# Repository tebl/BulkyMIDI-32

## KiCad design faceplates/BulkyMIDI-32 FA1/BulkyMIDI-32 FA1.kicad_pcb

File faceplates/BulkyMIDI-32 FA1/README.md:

# BulkyMIDI-32 Faceplate (FA1)
A faceplate designed to be installed onto the main [BulkyMIDI-32](https://github.com/tebl/BulkyMIDI-32/tree/main/BulkyMIDI-32%20Module)-module. The faceplate has provisions for mounting two of the buttons onto the faceplate, the signals passing through the pin headers in the top-left corner. I consider this more of a usability option as you're never in doubt what is up and down, but at the cost of having a cleaner finish on the faceplate itself. If all of this sounds rather horrible, then check out [Faceplate FA2](https://github.com/tebl/BulkyMIDI-32/tree/main/faceplates/BulkyMIDI-32%20FA2) as you might prefer that as an alternative.

- [1> Building the device](#1-building-the-device)
- [2> Schematic](#2-schematic)
- [3> BOM](#3-bom)

# 1> Building the device
Building the device should be a straight forward affair, you just solder the two components into place. Pay attention to keep the alignment somewhat straight, in particular the right-angle pin header needs to be flush against the board. A picture of the board is shown below, pay particular attention to which side the components are installed.

When installing the switches here, you'd jumper SW4 on the main BulkyMIDI-32 to positions 2-3 when doing so. The default would otherwise be linked across pins 1-2 when four buttons are installed on the main module instead.

The faceplate connects to the main module using extra long male pin headers, but we need to pay attention so that the height of these are adjusted before soldering them in place. The easiest way of doing this is just to insert them into the socket and press down on the faceplate until the black plastic part slides down into place. Once satisfied with the result, solder them in place and cut off the excess part of the pins that are poking out of the top.

# 2> Schematic
The supplied KiCad files should be sufficient as both a schematic and as a  starting point for ordering PCBs (basically you could just zip the contents of the export folder and upload that on a fabrication site), the schematic is also available in [PDF-format](https://github.com/tebl/BulkyMIDI-32/tree/main/documentation/schematic/faceplates) and this is what you'll need to print and work your way through when things fail to work as expected.

# 3> BOM
Most parts should be easy to get a hold of from your favourite local electronic component shop, but given that I don't have access to such shops where I live so everything was based on whatever I could get cheapest from eBay/AliExpress (free shipping, but plan on waiting 3-4 weeks for delivery). 

| Reference      | Item                                                  | Count | Order  |
| ---------------| ----------------------------------------------------- | ----- | ------ |
| Faceplate PCB  | Fabricate using Gerber files                          |     1 | [PCBWay](https://www.pcbway.com/project/shareproject/BulkyMIDI_32_Faceplate_FA1_22c4404e.html)
| J1             | 1x10 section of long male header pins                 |     1 |
| SW1,SW2        | 6x6x11mm right-angle momentary button                 |     1 |

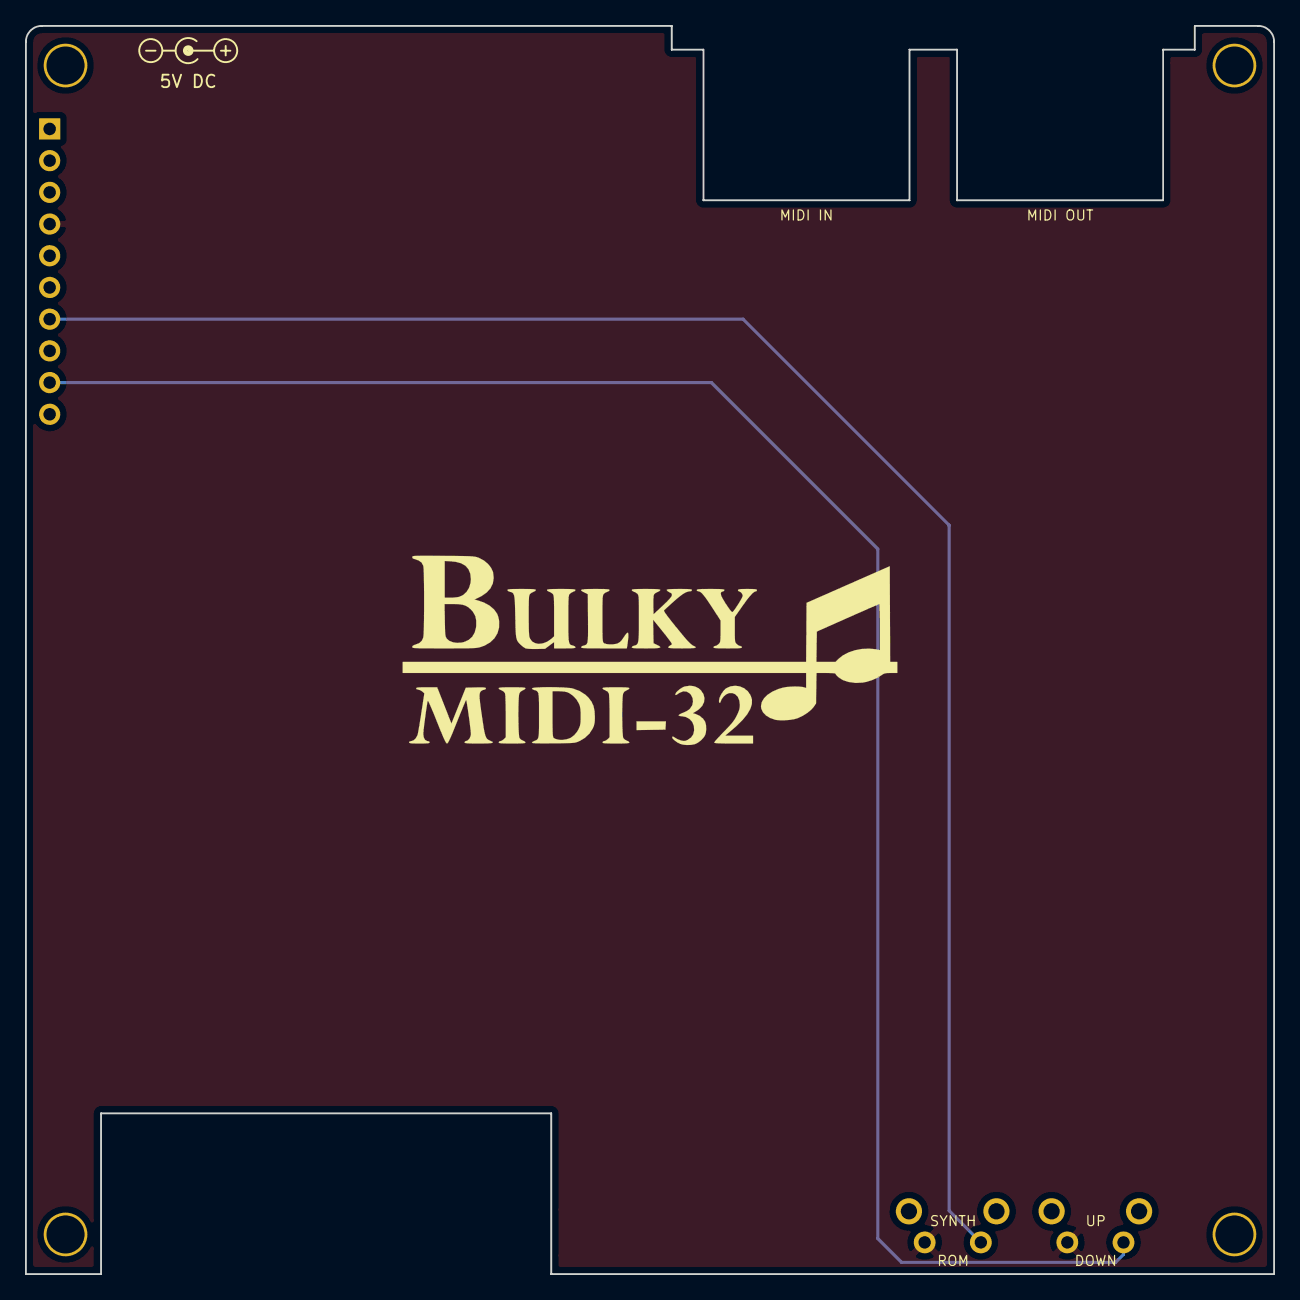
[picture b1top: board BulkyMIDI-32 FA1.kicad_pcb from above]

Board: 2 copper layers, 100.0 x 100.0 mm, 7 parts (1 on the bottom side), 3 nets.

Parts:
J4: Faceplate; PinHeader_1x10_P2.54mm_Vertical
M1, M2, M3, M4: Mounting; M3
SW1: SYNTH; SW_Tactile_SPST_Angled_PTS645Vx39-2LFS_Underside
SW4: VOL_UP; SW_Tactile_SPST_Angled_PTS645Vx39-2LFS_Underside

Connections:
GND: J4.4, SW1.1, SW4.1
SW_SYNTH: J4.7, SW1.2
SW_UP: J4.9, SW4.2
